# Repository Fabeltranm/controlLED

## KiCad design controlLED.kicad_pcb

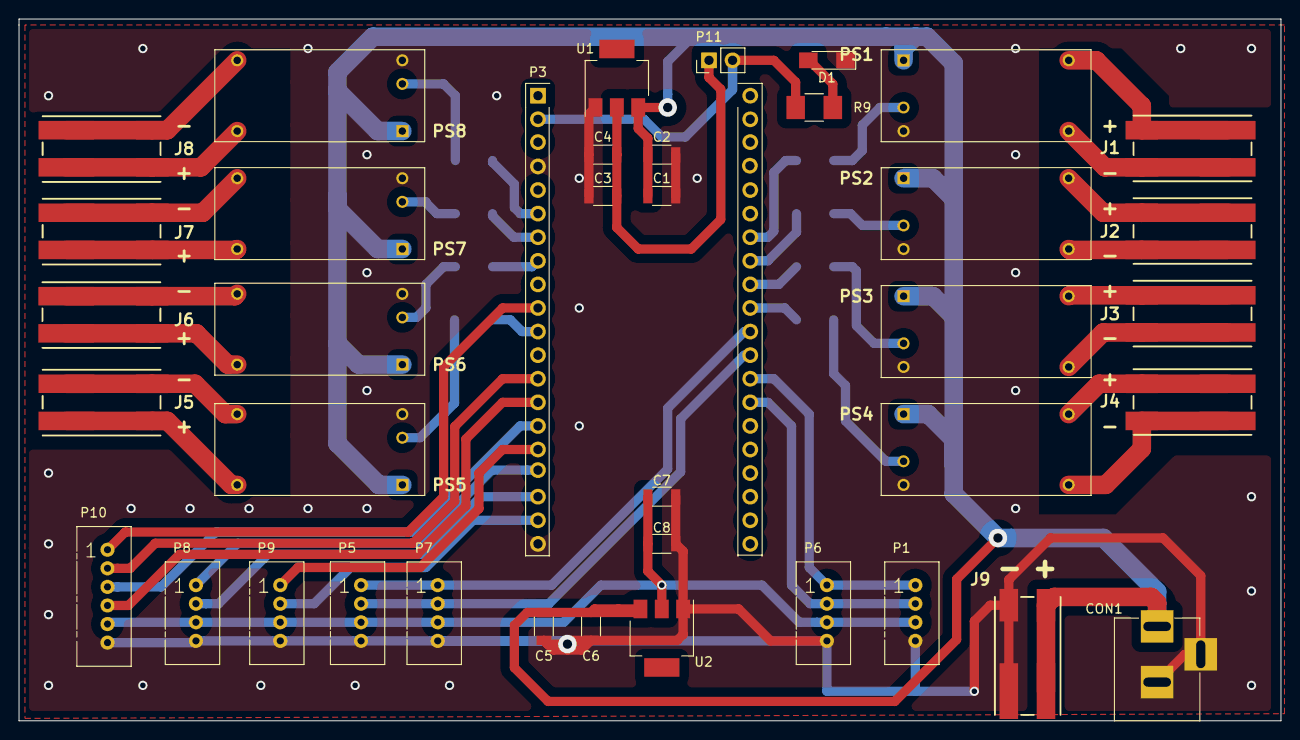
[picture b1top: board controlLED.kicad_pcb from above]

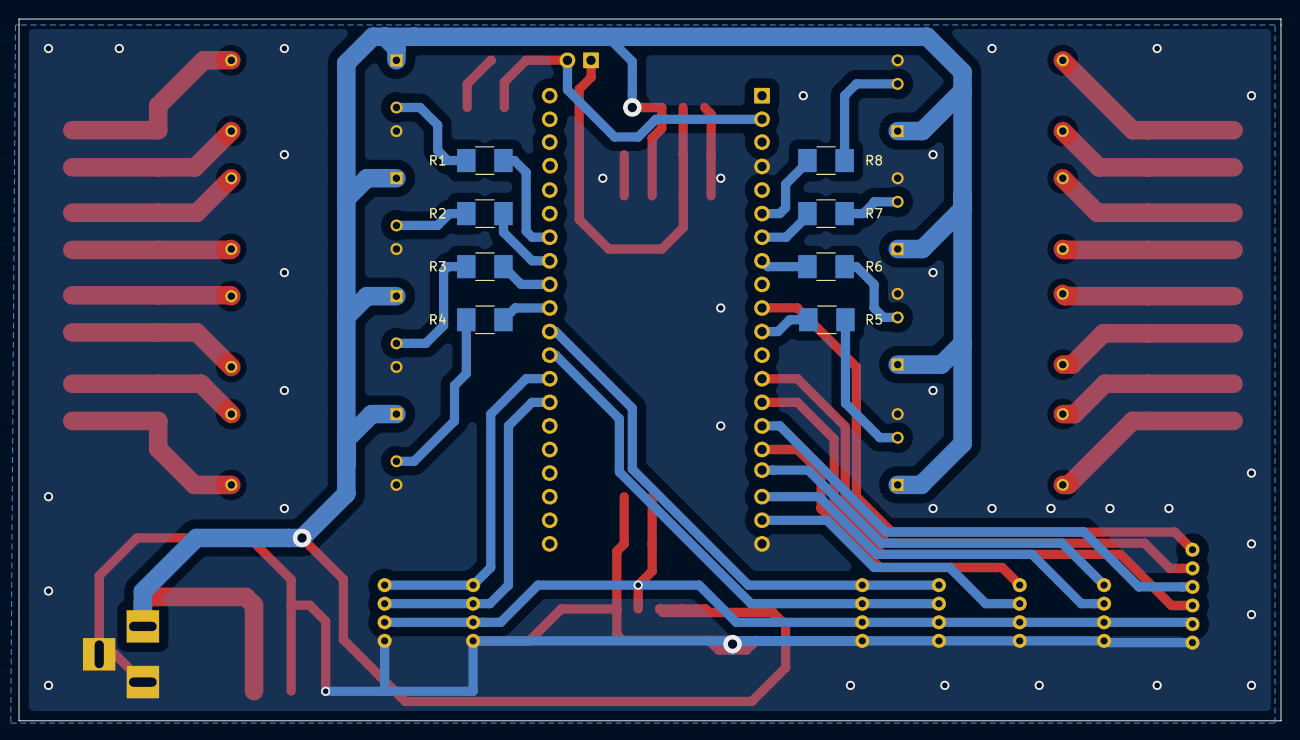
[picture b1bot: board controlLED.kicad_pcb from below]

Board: 2 copper layers, 135.9 x 75.6 mm, 47 parts (8 on the bottom side), 50 nets.

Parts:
C1, C2, C3, C4, C5, C6, C7, C8: C; C_1206
CON1: BARREL_JACK
D1: LED; LED_1206_HandSoldering
J1, J2, J3, J4, J5, J6, J7, J8, J9: connector; 2060-452998-404
P1, P6: CONN_A0-1; Grove_1x04
P3: ESP32_sparkfun; connect_esp32Thing
P5, P7: CONN_D0-1; Grove_1x04
P8: CONN_UART; Grove_1x04
P9: CONN_I2C; Grove_1x04
P10: CONN_01X06; Grove_1x06
P11: CONN_01X02; Pin_Header_Straight_1x02_Pitch2.54mm
PS1, PS2, PS3, PS4, PS5, PS6, PS7, PS8: LDD-300L; LDD-XXXL
R1, R2, R3, R4, R5, R6, R7, R8: 0ohm; R_1210_HandSoldering
R9: 1K; R_1210_HandSoldering
U1: LD1117S50TR; SOT-223
U2: LD1117S33TR; SOT-223

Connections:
/Ain1: P1.1, P3.33, P6.1
/Ain2: P1.2, P3.34, P6.2
/CS: P3.10, P10.1
/Din1: P3.31, P5.1, P7.1
/Din2: P3.32, P5.2, P7.2
/MISO: P3.15, P10.3
/MOSI: P3.14, P10.4
/PWM01: PS1.3, R1.1
/PWM02: PS2.3, R2.1
/PWM03: PS3.3, R3.1
/PWM04: PS4.3, R4.1
/PWM05: PS5.3, R5.1
/PWM05_: P3.11, R5.2
/PWM06: PS6.3, R6.1
/PWM06_: P3.8, R6.2
/PWM07: PS7.3, R7.1
/PWM07_: P3.7, R7.2
/PWM08: PS8.3, R8.1
/PWM08_: P3.6, R8.2
/RX: P3.17, P8.1
/SCL: P3.16, P9.1
/SCLK: P3.13, P10.2
/SDA: P3.19, P9.2
/TX: P3.18, P8.2
/VCC24: C1.1, C2.1, C5.1, C6.1, CON1.1, J9.1, J9.2, PS1.1, PS2.1, PS3.1, PS4.1, PS5.1, PS6.1, PS7.1, PS8.1, U1.3, U2.3
/VCC_1: C7.1, C8.1, P1.3, P5.3, P6.3, P7.3, P8.3, P9.3, P10.5, U2.2
GND: C1.2, C2.2, C3.2, C4.2, C5.2, C6.2, C7.2, C8.2, CON1.2, CON1.3, D1.1, J9.3, J9.4, P1.4, P3.4, P3.20, P5.4, P6.4, P7.4, P8.4, P9.4, P10.6, PS1.4, PS2.4, PS3.4, PS4.4, PS5.4, PS6.4, PS7.4, PS8.4, U1.1, U2.1
unnamed: C3.1, C4.1, P11.1, U1.2
unnamed: D1.2, R9.1
unnamed: J1.1, J1.2, PS1.6
unnamed: J1.3, J1.4, PS1.5
unnamed: J2.1, J2.2, PS2.6
unnamed: J2.3, J2.4, PS2.5
unnamed: J3.1, J3.2, PS3.6
unnamed: J3.3, J3.4, PS3.5
unnamed: J4.1, J4.2, PS4.6
unnamed: J4.3, J4.4, PS4.5
unnamed: J5.1, J5.2, PS5.6
unnamed: J5.3, J5.4, PS5.5
unnamed: J6.1, J6.2, PS6.6
unnamed: J6.3, J6.4, PS6.5
unnamed: J7.1, J7.2, PS7.6
unnamed: J7.3, J7.4, PS7.5
unnamed: J8.1, J8.2, PS8.6
unnamed: J8.3, J8.4, PS8.5
unnamed: P3.27, R1.2
unnamed: P3.28, R2.2
unnamed: P3.29, R3.2
unnamed: P3.30, R4.2
unnamed: P3.2, P11.2, R9.2

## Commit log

2019-03-20 ocb1
2019-03-21 pcb init
2019-04-10 version1.0
2019-04-10 version 1.0 s Please enter the commit message for your changes. Lines starting
